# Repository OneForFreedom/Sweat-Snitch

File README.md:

# Sweat-Snitch

Humidifier and Temp reader and projector, Top oled shows temp whilst bottom oled shows humidity. It also has a i2c multiplex because both oleds use the same lib.

A border of one px will show if temps are over 30 degrees C and a border of 4px will show if temps are over 40 degrees C

And no. This won't work if  you completely submerge it in water.

## Project Images

 ## BOM (Bill Of Materials)

| Item                | Quantity | Unit Price (USD) | Total Price (USD) | Link                        |
| ------------------- | -------- | ---------------- | ----------------- | --------------------------- |
| PCB                 | 1        | 37.76            | 37.76             | [link](https://jlcpcb.com) |
| 120x64 OLED         | 1        | 8.36             | 8.36              | [link](https://www.aliexpress.com/item/1005009059402520.html?spm=a2g0o.cart.0.0.54c038da04MvbX&mp=1&pdp_npi=5%40dis%21USD%21USD%209.20%21USD%208.36%21%21USD%208.36%21%21%21%4021038da617629913850046188e4225%2112000047762448537%21ct%21UK%216063356903%21%211%210) |
| 32x128 OLED         | 1        | 6.95             | 6.95              | [link](https://www.aliexpress.com/item/1005008918700196.html?spm=a2g0o.cart.0.0.54c038da04MvbX&mp=1&pdp_npi=5%40dis%21USD%21USD%208.17%21USD%206.95%21%21USD%206.81%21%21%21%4021038da617629913850046188e4225%2112000047202792620%21ct%21UK%216063356903%21%211%210) |
| TCA9548A            | 1        | 3.87             | 3.87              | [link](https://www.aliexpress.com/item/1005007045955724.html?spm=a2g0o.productlist.main.33.76691rzg1rzg7r&algo_pvid=0d004523-b776-46f6-858b-fdce07ac84ff&algo_exp_id=0d004523-b776-46f6-858b-fdce07ac84ff-30&pdp_ext_f=%7B%22order%22%3A%227%22%2C%22eval%22%3A%221%22%2C%22fromPage%22%3A%22search%22%7D&pdp_npi=6%40dis%21GBP%211.07%210.97%21%21%211.36%211.23%21%40211b615317629902107267153ea55b%2112000039209725776%21sea%21UK%216063356903%21X%211%210%21n_tag%3A-29919%3Bd%3A3fd4c7f7%3Bm03_new_user%3A-29895&curPageLogUid=Wrrspp4YM6PT&utparam-url=scene%3Asearch%7Cquery_from%3A%7Cx_object_id%3A1005007045955724%7C_p_origin_prod%3A) |
| Seeed Studio RP2040 | 1        | 8.74            | 8.74             | [link](https://thepihut.com/products/seeed-xiao-rp2040?variant=53975380263297) |
| **Total**           |          |                  | **65.68**         |                             |

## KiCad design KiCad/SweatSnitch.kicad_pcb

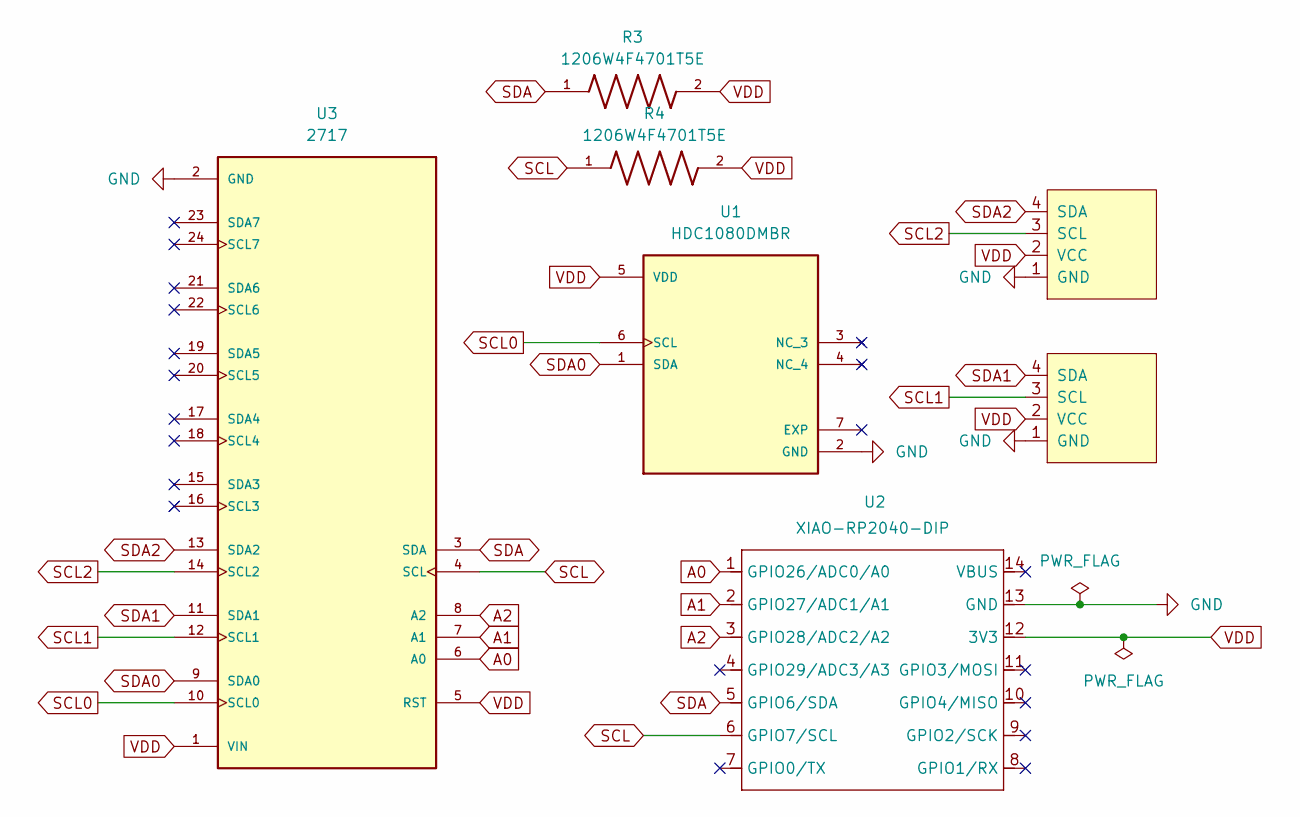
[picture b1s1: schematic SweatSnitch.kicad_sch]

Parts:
Brd1: SSD1306; 128x64OLED
Brd2: SSD1306; SSD1306-0.91-OLED-4pin-128x32
R3, R4: 1206W4F4701T5E; RESC3115X65N; PARTREV V3
U1: HDC1080DMBR; SON100P300X300X80-7N; PARTREV A
U2: XIAO-RP2040-DIP
U3: 2717; MODULE_2717; PARTREV Sep 11, 2015

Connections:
A0: U2.1 (GPIO26/ADC0/A0), U3.6 (A0)
A1: U2.2 (GPIO27/ADC1/A1), U3.7 (A1)
A2: U2.3 (GPIO28/ADC2/A2), U3.8 (A2)
GND: Brd1.1 (GND), Brd2.1 (GND), U1.2 (GND), U2.13 (GND), U3.2 (GND)
SCL: R4.1, U2.6 (GPIO7/SCL), U3.4 (SCL)
SCL0: U1.6 (SCL), U3.10 (SCL0)
SCL1: Brd1.3 (SCL), U3.12 (SCL1)
SCL2: Brd2.3 (SCL), U3.14 (SCL2)
SDA: R3.1, U2.5 (GPIO6/SDA), U3.3 (SDA)
SDA0: U1.1 (SDA), U3.9 (SDA0)
SDA1: Brd1.4 (SDA), U3.11 (SDA1)
SDA2: Brd2.4 (SDA), U3.13 (SDA2)
VDD: Brd1.2 (VCC), Brd2.2 (VCC), R3.2, R4.2, U1.5 (VDD), U2.12 (3V3), U3.1 (VIN), U3.5 (RST)

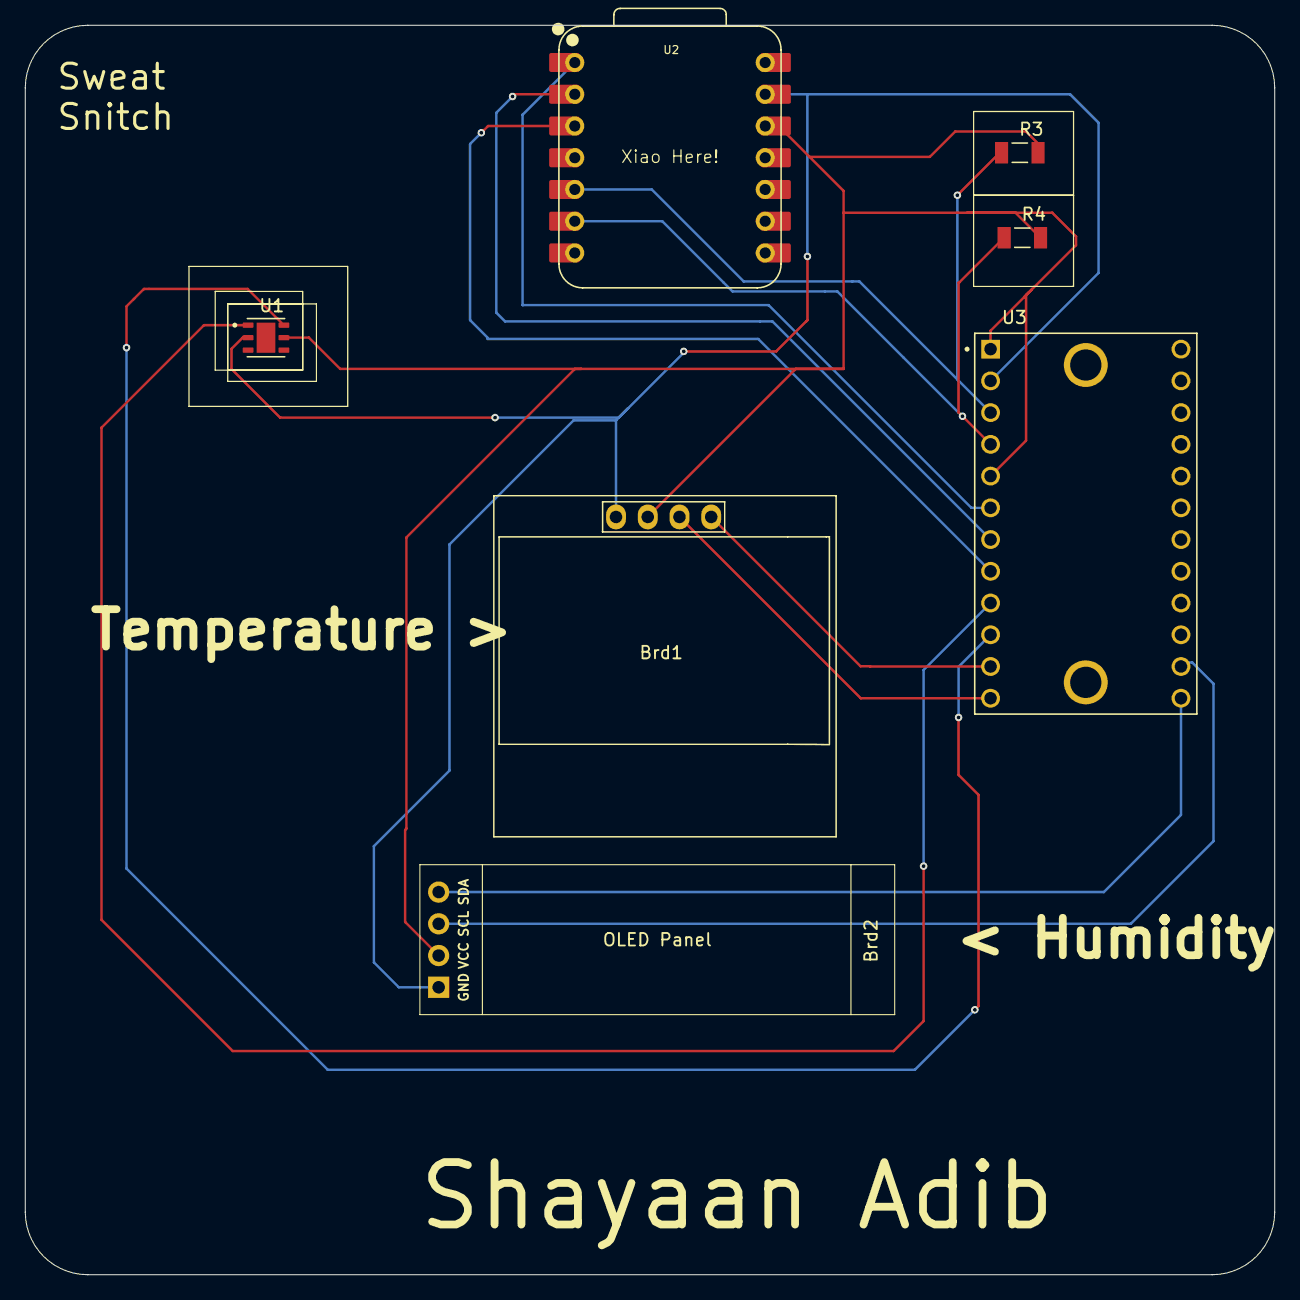
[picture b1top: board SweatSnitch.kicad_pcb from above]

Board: 2 copper layers, 100.0 x 100.0 mm, 7 parts (0 on the bottom side), 13 nets.

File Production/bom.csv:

Designator,Footprint,Quantity,Value,LCSC Part #
BRD1,128x64OLED,1,SSD1306,
"R3, R4",RESC3115X65N,2,1206W4F4701T5E,
U1,SON100P300X300X80-7N,1,HDC1080DMBR,
U2,XIAO-RP2040-DIP,1,XIAO-RP2040-DIP,

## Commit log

2025-07-29 Rename SweatSnitch.zip to Production/SweatSnitch.zip
2025-07-29 Rename SweatSnitch.kicad_pro to KiCad/SweatSnitch.kicad_pro
2025-07-29 Rename Screenshot 2025-07-30 002246.png to Images/3D F
2025-07-29 Rename 3D F to 3D F.png
2025-07-29 Rename Screenshot 2025-07-30 002254.png to 3D B.png
2025-07-29 Rename Screenshot 2025-07-30 002506.png to Schematic.png
2025-07-29 Rename Schematic.png to PCB.png
2025-07-29 Rename Screenshot 2025-07-30 002600.png to Schematic.png
2025-07-29 Rename SweatSnitch.ino.ino to SweatSnitch.ino
2025-07-29 Rename SweatSnitch.ino.ino to Firmware/SweatSnitch.ino
2025-11-11 Add initial journal entry for Sweat-Snitch project
2025-11-12 Update JOURNAL.md with project progress and plans
    Expanded on the pull-up system description and added details about hardware experience and time spent. Updated plans for future tasks including BOM and PCB corrections.
2025-11-12 Update JOURNAL.md with project progress and details
    Refined pull-up system description and updated project details.
2025-11-12 Revise final journal entry for better readability
    Formatted final entry for clarity and consistency.
2025-11-12 Add BOM section to README.md
2025-11-13 Update Bom.csv with new items and pricing
    Added items with quantities, prices, and links to Bom.csv.
2025-11-13 Revise time spent on project in JOURNAL.md
    Updated time estimates for project completion.
2025-11-13 Update PCB image in README
    Replaced PCB image with an external image link.
